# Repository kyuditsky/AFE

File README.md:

AFE 230V 16A

Phoenix Contact
BC Modular Housing

AFE 230v_16a buildnotes
addendums at bottom

1/14/25

***

https://media.digikey.com/pdf/data%20sheets/phoenix%20contact%20pdfs/bc_series_installation_component_housing.pdf

***

***

https://github.com/erichelgeson/Kicad-STM32
add legacy symbols:
symbol editor > File > import

manage symbols > migrate

***

BC71,6 OT-U11

i/o
---
MSTBVA_2,5_2-G-5,08		#LPC 2,5/2-ST-5,08	plug 16A / 320V
				#1792757		12A / will actually fit
				#MVSTBW 2,5/ 2-ST-5,08
j1	VO_pn
j2	K_io
j3	I_pn

MCV_1,5_6-G-3.81
j4	DGND
	3v3
	A0
	A1
	A2
	D0

footprints
TSOT-23-5	opamps
SOT-23		regulator
SOIC-7		optocoupler
SOIC-8		currentsensee

A5?		#A2
3v3in?

***
1/15/25
Blackpill STM32 will be on separate daughterboard

added HBUS connector to schema

***
HBUS-B SET BK - Protective cap
2278173
***

Spec:
Contact 1..4	power
contact 5..16	signal
Air clearances and creepage distances
... to the DIN rail At least 0.23 mm
... between one another At least 0.13 mm
... between power and signal At least 0.8 mm
Current carrying capacity for each contact
3 A, maximum total current 25 A

***
1/16/25

generated BOM from schema
refined layout and i/o port locations

request to swap A2 to A0 and slide down accordingly
	basically current on the left, voltage on right
	of J4

***
1/23/25

Housing:

HBUS 71,6-16P-1S BK - DIN rail bus connectors	2896296		#digikey 10 instock - 33.54

full set
BC 71,6-SKT-U11-7035+4SPTA6 - Housing set	1456985		#larger space on PCB2-8
								#11mm connector space on PCB1

Base:
BC 71,6 UT HBUS BK - Mounting base housing	2896267		#8.53

upperhousing UT11
BC 71,6 OT U11 KMGY - Upper housing part	2896050		#5.66

housing cover:
BC 71,6 DKL S TRANS - Housing cover		2896128		#4.93

inter-PCB connection:

ESW-106-12-G-D		6 pos, 11.05mm above pcb, gold plated, double row (12pos total)
			2.54 pitch, THT

2.54 pin header		underside of connecting pcb
			
	11.05mm + 2.54mm = 	13.59mm stack height
				perfect stack from pcb1 to pcb4

***
1/24/25

added copper pours from current i/o to U5

blackpill pinout in PCBnew appears incorrect to documentation

footprint matches:
	https://uglyduck.vajn.icu/STM32_Pills/BlackPill_STM32F103_Pinout.jpg

current blackpill:
	https://cdn-shop.adafruit.com/970x728/4877-03.jpg

updated with:
	https://github.com/MSZ98/Blackpill-KiCad-library

STEP files imported into Fusion

	MCV_1,5_6-G-3.81 	&	MCVR 1,5/ 6-ST-3,81
	1803468				1827169
		will not work, move socket towards pcb edge

	MSTBVA_2,5_2-G-5,08	&	MVSTBW 2,5/ 2-ST-5,08
	1755736				1792757
		will NOT work
		connectors should rotate
		and new connector should be chosen

Fillets on main PCB edges are only needed if filler plugs are to be used

SPTAF 1/ 5-3, 5-IL	supplied with housing kit, 11mm deep
	16A 160V

1862275
SPTAF 1/ 2-5,0-IL	2 terminal
	16A 320V	made to order	in stock at mouser
			IL vs EL

SPTAF 1/ 4-5,0-EL	4 terminal	#use 6 terminal for signal i/o
1862437			

AC inputs should be at least 2.5mm wire

***
https://electronics.stackexchange.com/questions/645255/4-layer-board-clearance-and-stack-up-for-230v

creepage / clearance

remove gnd plane from around I_inputs & Vp/n

***
1/27/25

SPTAF 1/ 6-5,0-EL
1862453

2202302 upper housing 11,11,22,00	restricted availability

in order to use SPTA-THR 2,5/ 6-5,0 P26		#for 12 awg wire AC inputs
need to swtich to UT22 upperhousing

1071206
SPTA-THR 1,5/ 6-5,08 R56	#might work, wire size 16awg
				#nonstocked at mouser
				#instock at digikey

***
02/02/25

Mouser Order sent			order#273566739

ordered two MKDSN 1.5/2-HT		1985849		rated 13A/320v
	for Ki/o
AC inputs: MKDSN 2.5/3-5.08-BK		1800882		
	(2.5/6 out of stock)
Signal Out: MKDS 1.5/6			1715190

********

02/06/25

revisiting pcb2-8
	& headers between
	see 01/23/25		#ESW-106-12-G-D

JLCPCB standard pcb thickness = 1.6mm

space between each:

pcb1-2	3,55mm
pcb2-3	3,45
pcb3-4	3,45
pcb4-5	3.45		#if blackpill is socketed, void pcb5-8
pcb5-6	3,45
pcb6-7	0,95
pcb7-8	-0.3		#pcb7&8 cannot co-exist
pcb8-9	1.25		#pcb9 replaces fitted cover

>>>pcb1 edge dimensions are incorrect
	edge cutouts in middle are too deep
	HBUS connector is in the wrong spot
>>fixed hbus placement
	did not change edgecuts
	current edge cut and drawing differ 0,45mm	
		#radius of curve 1,2mm but edges are 0,75mm offset
		#hbus location callout uses the 0,75mm line

considering shifting intrapcb connector to the left	#implemented
	reasoning: allows for pcb 2 to be installed (cutout is close to mounting fin ~1.5mm)

****
02/16/25

added pcb5-7 with kludge and copper pours
added kludge to other pcbs

added silkscreen on pcb9

****

02/27/25

PCBs arrived, Parts arrived
putting it together:

pcb8 does not fully lock into bottom case
	top base needs a support remove as well
	*use pcb7 instead (may still need to remove support
	pcb8 gnd plane net is wrong

overall, edgecuts are correct

c1-2 are 0402?		#my bad
	footprint is 0603

the intrapcb connectors looks good
make cutout in pcb2,3 larger, but fits for now

U4, solidstate relay, just barely fits under pcb2

typical female 2.54mm header, from pcb1 to pcb3, stacks directly underpcb3

	pcb3-pcb5 approximately the same thing
	could probably use pcb1, 3, & 5 for a 3 board arrangement

****
05/05/25 - meeting

issues soldering the ground plane pads - with thermal relief

plan to design to pick and place, still jlcpcb?
	mitigate some of the issues possibly due to soldering

testing feels like a waste of time, i dont always know what im looking at

dont have a good grasp of the details of the scope

single ended two op amps, gnd and point
	A0 and A1 subtract one from another to get ------

differential has 3 op amp
	does the subtraction

single
a0 ref to gnd
a1 ref to gnd
	note divider from 3V to GND to give 1.5v at input buffer

diff r19 r21 should be 500, r20 1k
r22 r23 dnp

everycircuit - simulator

testing setup >>
single ended (two opamp)
	wavegen 1 & gnd to V0p & V0n
	scope 1+ to A0			1+ 
	scope 1- to A1			scope 1- to dgnd
	3v3V+ to 3v3
	gnd to DGND
waveform passed through without power to board
	1.5v observed at r35/r36

differential
	wavegen 1 & gnd to V0p & V0n
	scope 1+ to A0
	scope 1- to dgnd
	3v3V+ to 3v3
	gnd to DGND
	
	0.6v observed at r35/r36
***	
	r22/r23 should be DNP
	r19/r21 should be 500ohm

****
updated guidance:
Focus on single ended:

	two sides are separate paths, test 1 path at a time
	
	V0p - wave to A0 - scope
	scope1- to dgnd

	V0n - wave to A1 - scope
	scope1- to dgnd

	(need to check for 1.5V at r15/r17; r16/18)

07/09/25

differential board, 3 opamps
	depopped r22, r21
	lifted a trace near r22, 
		determined iron too hot with narrower tip

Lifted R19 pads while desoldering
	buss wired from R20 to U1-4 & R22
		cut old R22 trace to A0
		R19 is now on R22 pads
		replaced to 510ohm
R21 now 510ohm
R20 in place at 1k

hot glue placed over cut A0 trace
	(exposed gnd plane)

*******
08/13/25 10:00a

identify and order just the differential parts
	to be tested via V0/V1_sense on HBUS footprint
	using the digilent waveform gen

initial DNP:	
	r1-12 	voltage dividers 
	d1-4	zener diodes
	c1 c2	capacitors	sized up to 0603

V0_sense starts: 	
	r13 	499k ohm 	#consider a 0ohm resistor
	c1	1nf
	r15 	20k (to 3vREF)	#Voltage divider to non-inverting input U1
	r17	20k (to gnd)
	r19	510		#feedback R
	
	r24	1k		#buffer to non-inverting U3
	r27	1k		#buffer to 1.5vREF	(r35&r36 20k divider)

V1_sense starts:
	r14 	499k ohm 	#consider a 0ohm resistor
	c2	1nf
	r16 	20k (to 3vREF)	#Voltage divider to non-inverting input U2
	r18	20k (to gnd)
	r21	510		#feedback R
	
	r25	1k		#buffer to inverting U3
	r26	1k		#U3 feedback

common components:

	U1-3	AD8528		#opamps		TSOT23-5
	d1-4	pdz36b		#36v zener diodes, order but dnp

	r20	1k		#ties both sides together
	r35	20k		#1.5vREF
	r36	20k		#1.5vREF
	U7	REF3030		#3V regulator	SOT23

	r39	0		#gnd to dgnd
	C5,6,10	0.1uF		#filtercaps

notes:
	look at r20 net, should it be connected directly to output of u1
		#sent to nathan
		confirms r20 should bridge U1 out to U2 out
		updated PCBnew

	populate PCB a few components at a time & test
		looking at you 1.5vREF

AFE_230v_16a rev.2 aug25
	changelog
	
	changed r20 to u1 & u2 outputs
	added thermal relief to D1 D2 earth connections
	added thermal relief to I_p & I_n fill zones
	rotated U4 to keep traces on F.cu
	added AVDD indicator LEDs to main pcb

2pm
lets order the updated pcb and mouser components by end of day

	look into jlcpcb pick and place and smaller components (0402)

AFE_diff_schematic
	focus on just the differential section
		using 0402 components
****
new plan (again)
	we are ordering a new pcb (because of R20)
	pick and place the components on the new pcb (adjust footprints accordingly)
		keeping all R footprints for now, all C footprints are 0603

	U1-3, U6, LEDs, & R29 non- placeable
	D1-4 are extended ($3.00 per extended component type)
	U7 is extended, opted out

	ordering 5 boards, populating 2 ($0.75 more to populate 5 as opposed to 2)
				and rev1 single end works without revision
				but. lets keep some blank boards
	16.17 for pcb+pcba
	9.97 shipping
	-9.00 coupon
	total: 18.05

***

08/18/25
	plan to order female pin headers from Adafruit

	leave off R34 from auto-populating
		or add 0 ohm jumper

	need to organize spreadsheets better

****
09/08/25

ordered more microhook test leads

looking over mouser order

	AC signal inputs - 1
	Signal Outputs - 1
	K i/o - 2

	opamps - 10
	U4 Relay - 1
	U7 3v ref - 5
	U5 current sense - 2
	R29 big R - 4
	
	pcb4 elevated socket - 2

R20 could have been rerouted without a via to B.Cu
removed thermal relief from Ip,In

dont auto-populate r30,r31 (only pop for opamp current sensing with r29)

test before populating r1-12 (voltage dividers)

r13,14, r22,23 will need hand populating (extended componenets)
	#should not have popped r22,r23, but will test waveform thru A0,A1
5v,3v3 LED hand pop

header pins as needed
	V1/V0 test points
	DGND > D0 header
		dgnd, 3v, A0,A1,A2,D0

3v3, 5v LED test good

3v3 supply, no opamps
	3.317v at 3v3
	2.997v at 3vref
	1.483v at 1.5vref

#same divider but different nets?
#1.5vref and r15/r17 & r16/r18

power looks good, continueing to add opamps

Should not have popped r22,r23 for differential setup, but will test waveform thru A0,A1
	V0_sense thru to A0
	V1_sense thru to A1
		both test good without power to board, no offset

		with 3v3 power to board, look good, adds a 1.46v(A0) & 1.47v(A1) offset
			with or without waveform input (5v amplitude)
			scope range 1v/div

going to remove r22,r23
	r22,23 depopped without trouble

3v3 supply, opamps installed
r27, 1.5vref = 1.497v
3v0ref = 3.0v
3v3 = 3.317v
1.5vref = 1.497v (r35/r36)

power still looks good

3v3 to board

W1 to V0_sense
W2 to V1_sense

1+ to A0
1- to dgnd

no longer the 1.5v offset
	output (A0) looks promising, especially with Sine wave inputs
	scope range needs to be dialed down to 100mV/div or less

can add 
	Vin dividers (r1-12)
	input/signal I/O
	blackpill header
	Ki/o relay
& option for either 
		current sense IC (depop r30,31)
		or R29 & opamp

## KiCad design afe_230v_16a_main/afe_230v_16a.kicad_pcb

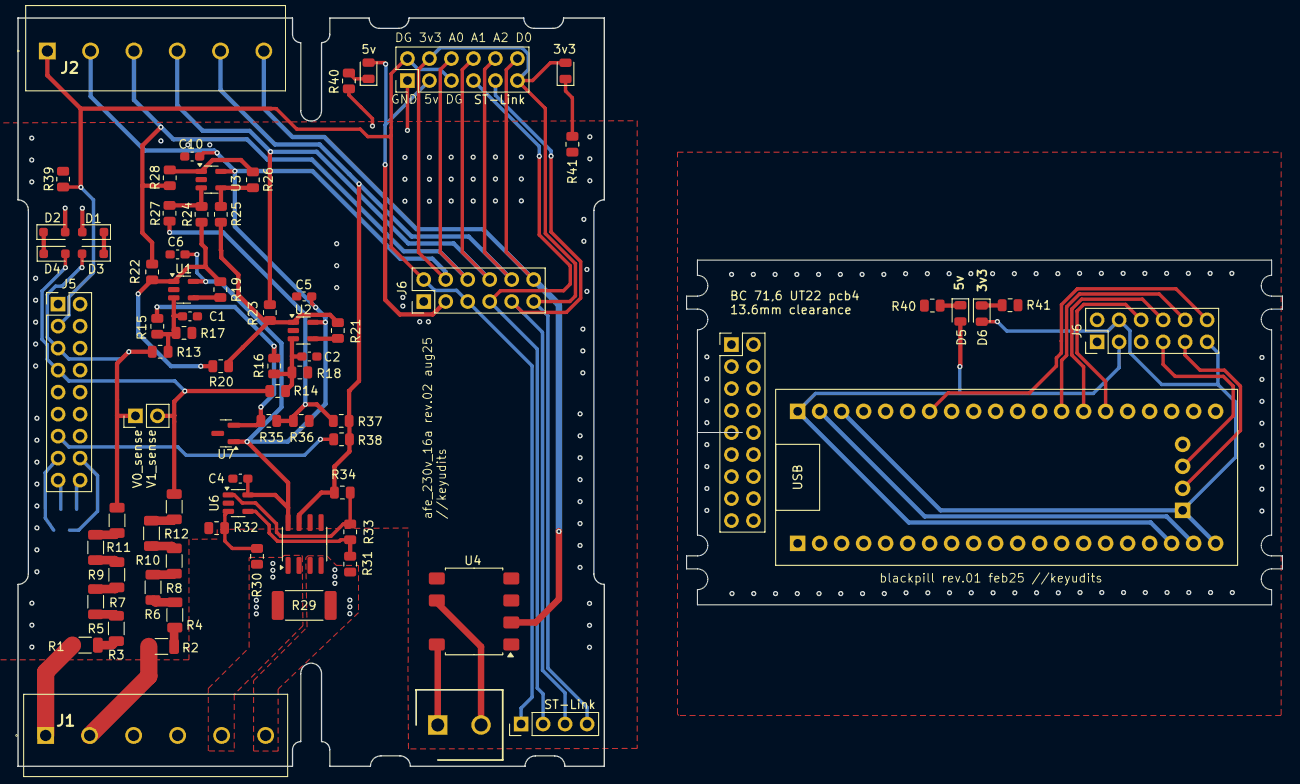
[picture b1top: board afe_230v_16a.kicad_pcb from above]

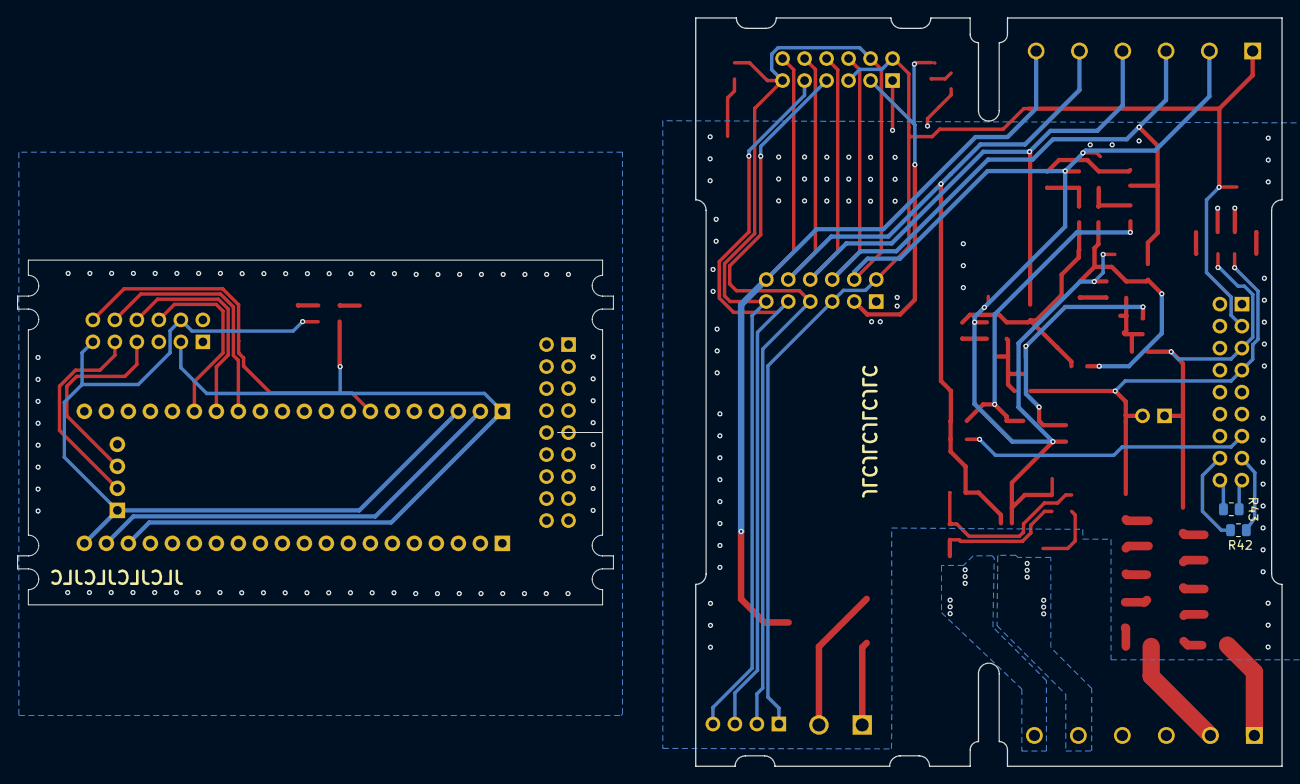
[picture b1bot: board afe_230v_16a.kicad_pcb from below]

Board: 2 copper layers, 145.9 x 86.4 mm, 76 parts (2 on the bottom side), 61 nets.

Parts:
3v3, 5v: LED; LED_0805_2012Metric
C1, C2: 1nF; C_0603_1608Metric_Pad1.08x0.95mm_HandSolder
C4, C5, C6, C10: 0.1uF; C_0603_1608Metric_Pad1.08x0.95mm_HandSolder
D1, D2, D3, D4: PDZ36B; D_SOD-323_HandSoldering
D5, D6: LED; LED_0805_2012Metric
J1: MKDSN 2,5/ 6-5,08; 1989405
J2: MKDS 1,5/ 6; 1715190
J5, J5#2: HBUS16; PinHeader_2x09_P2.54mm_Vertical
J6, J6#2, J6#3: pinheader_2x6_socket; PinHeader_2x06_P2.54mm_Vertical
J**: SHDR2W130P0X500_1X2_1000X810X1000P; 1985849_SHDR2W130P0X500_1X2_1000X810X1000P
R1, R2, R3, R4, R5, R6, R7, R8, R9, R10, R11, R12: 680K; R_1206_3216Metric
R13, R14: 499K; R_0805_2012Metric
R15, R16, R17, R18, R35, R36: 20K; R_0805_2012Metric
R19, R21: 0K; R_0805_2012Metric
R20, R24, R25, R26, R27, R28: 1K_dnp; R_0805_2012Metric
R22, R23: 33R2; R_0805_2012Metric
R29: 0R005; R_2512_6332Metric_Pad1.40x3.35mm_HandSolder
R30, R31, R32, R33, R34, R37: 1KR; R_0805_2012Metric
R38: 0K_dnp; R_0805_2012Metric
R39, R42, R43: 0; R_0805_2012Metric
R40, R40#2, R41, R41#2: 2.2k; R_0805_2012Metric
ST-Link: Conn_01x04_STlink_pinheader; PinHeader_1x04_P2.54mm_Vertical
U1: TSOT-23-5
U2: AD8538; TSOT-23-5
U3, U6: AD8538_dnp; TSOT-23-5
U4: AQH3223A; SSO-7-8_6.4x9.78mm_P2.54mm
U5: ACS711xLCTR-25AB; SOIC-8_3.9x4.9mm_P1.27mm
U7: REF3030; SOT-23
U10: BlackPill_F4_SWI; Blackpill_F4_SWI

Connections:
/1V5_REF: R27.2, R35.1, R36.2, R37.2
/3V0_REF: R15.2, R16.2, R35.2, U7.2 (OUT)
/3V3: 3v3.2 (A), C4.1, C5.1, C6.1, C10.1, D6.2 (A), J2.2, J6.4, J6.11, J6#2.4, J6#2.11, J6#3.4, J6#3.11, ST-Link.4, U1.5 (V+), U2.5 (V+), U3.5 (V+), U5.8 (VCC), U6.5 (V+), U7.1 (IN), U10.20 (3V3), U10.38 (3V3), U10.41 (3V3)
/5v: 5v.2 (A), D5.2 (A), J6.3, J6#2.3, J6#3.3, U10.18 (5V), U10.40 (5V)
/15a: J5.15, J5#2.15, R42.1
/15b: J5.16, J5#2.16, R42.2
/16a: J5.17, J5#2.17, R43.1
/16b: J5.18, J5#2.18, R43.2
/24V: J5.1, J5#2.1
/A0: J2.3, J6.6, J6#2.6, J6#3.6, R22.2, R28.2, U10.26 (A0)
/A1: J2.4, J6.8, J6#2.8, J6#3.8, R23.2, U10.27 (A1)
/A2: J2.5, J6.10, J6#2.10, J6#3.10, R34.2, R37.1, R38.1, U5.7 (VIOUT), U10.28 (A2)
/CAN_hi: J5.9, J5#2.9
/CAN_lo: J5.11, J5#2.11
/D0: J2.6, J6.12, J6#2.12, J6#3.12, U4.2, U10.34 (B0)
/DGND: J2.1, J5.3, J5#2.3, J6.2, J6.5, J6#2.2, J6#2.5, J6#3.2, J6#3.5, R39.2, ST-Link.1
/DIO: J6.9, J6#2.9, J6#3.9, ST-Link.3, U10.42 (SWDIO)
/I0_sense: J5.13, J5#2.13, R38.2
/I_n: J1.6, R29.2, R31.2, U5.3 (IP-), U5.4 (IP-)
/I_p: J1.5, R29.1, R30.1, U5.1 (IP+), U5.2 (IP+)
/K0_on: J5.2, J5#2.2
/K0_status: J5.6, J5#2.6
/K1_on: J5.4, J5#2.4
/K1_status: J5.8, J5#2.8
/K_i: J**.1, U4.8
/K_o: J**.2, U4.6
/SCK: J6.7, J6#2.7, J6#3.7, ST-Link.2, U10.43 (SWCLK)
/V0_n: J1.2, R2.1
/V0_p: J1.1, R1.1
/V0_sense: D3.2 (A), J5.5, J5#2.5, R11.2, R13.1
/V1_sense: D4.2 (A), J5.7, J5#2.7, R12.2, R14.1
/V2_sense: J5.10, J5#2.10
/V3_sense: J5.12, J5#2.12
/V4_sense: J5.14, J5#2.14
Earth: C1.2, C2.2, C4.2, C5.2, C6.2, C10.2, D1.2 (A), D2.2 (A), J6.1, J6#2.1, J6#3.1, R17.1, R18.1, R32.2, R36.1, R39.1, R40.1, R40#2.1, R41.1, R41#2.1, U1.2 (V-), U2.2 (V-), U3.2 (V-), U4.1, U4.3, U4.4, U5.5 (GND), U6.2 (V-), U7.3 (GND), U10.19 (G), U10.39 (G), U10.44 (GND)
unnamed: D1.1 (K), D3.1 (K)
unnamed: D2.1 (K), D4.1 (K)
unnamed: 5v.1 (K), D5.1 (K), R40.2, R40#2.2
unnamed: 3v3.1 (K), D6.1 (K), R41.2, R41#2.2
unnamed: R1.2, R3.1
unnamed: R2.2, R4.1
unnamed: R3.2, R5.1
unnamed: R4.2, R6.1
unnamed: R5.2, R7.1
unnamed: R6.2, R8.1
unnamed: R7.2, R9.1
unnamed: R8.2, R10.1
unnamed: R10.2, R12.1
unnamed: R9.2, R11.1
unnamed: R19.2, R20.1, R22.1, R24.1, U1.1
unnamed: R20.2, R21.2, R23.1, R25.1, U2.1
unnamed: R26.2, R28.1, U3.1
unnamed: R33.2, R34.1, U6.1
unnamed: C1.1, R13.2, R15.1, R17.2, U1.3 (+)
unnamed: R19.1, U1.4 (-)
unnamed: C2.1, R14.2, R16.1, R18.2, U2.3 (+)
unnamed: R21.1, U2.4 (-)
unnamed: R24.2, R27.1, U3.3 (+)
unnamed: R25.2, R26.1, U3.4 (-)
unnamed: R30.2, R32.1, U6.3 (+)
unnamed: R31.1, R33.1, U6.4 (-)

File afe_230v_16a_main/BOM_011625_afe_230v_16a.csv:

"Reference","Value","Datasheet","Footprint","Qty","DNP"
"C1,C2","1nF","~","Capacitor_SMD:C_0402_1005Metric","2",""
"C3,C7,C8,C9,C12,J1,J2,J3,T7,T8,T9,T10,T11,T16,T17","~","-- mixed values --","-- mixed values --","15",""
"D1,D2,D3,D4","PDZ36B","~","Diode_SMD:D_SOD-323F","4",""
"J4","MCV 1,5/ 6-G-3,81","~","Connector_Phoenix_MC:PhoenixContact_MCV_1,5_6-G-3.81_1x06_P3.81mm_Vertical","1",""
"J5","HBUS16","~","Connector_PinHeader_2.54mm:PinHeader_2x09_P2.54mm_Vertical","1",""
"P1","06-14-03_rectifier","","","1",""
"R1,R2,R3,R4,R5,R6,R7,R8,R9,R10,R11,R12","680K","~","Resistor_SMD:R_1206_3216Metric","12",""
"R13,R14","499K","~","Resistor_SMD:R_0805_2012Metric","2",""
"R15,R16,R17,R18,R35,R36","20K","~","Resistor_SMD:R_0805_2012Metric","6",""
"R19,R21","0K","~","Resistor_SMD:R_0805_2012Metric","2",""
"R20,R24,R25,R26,R27,R28","1K_dnp","~","Resistor_SMD:R_0805_2012Metric","6","DNP"
"R22,R23","33R2","~","Resistor_SMD:R_0805_2012Metric","2",""
"R29","0R005","~","Resistor_SMD:R_2512_6332Metric_Pad1.40x3.35mm_HandSolder","1",""
"R30,R31,R32,R33,R34,R37","1KR","~","Resistor_SMD:R_0805_2012Metric","6",""
"R38","0K_dnp","~","Resistor_SMD:R_0805_2012Metric","1","DNP"
"U1","","https://www.analog.com/media/en/technical-documentation/data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","Package_TO_SOT_SMD:TSOT-23-5","1",""
"U2","AD8538","https://www.analog.com/media/en/technical-documentation/data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","Package_TO_SOT_SMD:TSOT-23-5","1",""
"U3,U6","AD8538_dnp","https://www.analog.com/media/en/technical-documentation/data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","Package_TO_SOT_SMD:TSOT-23-5","2","DNP"
"U4","AQH3223A","https://mediap.industry.panasonic.eu/assets/imported/industr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","Package_SO:SSO-7-8_6.4x9.78mm_P2.54mm","1",""
"U5","ACS711xLCTR-25AB","http://www.allegromicro.com/~/Media/Files/Datasheets/ACS711-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","Package_SO:SOIC-8_3.9x4.9mm_P1.27mm","1",""
"U7","REF3030","http://www.ti.com/lit/ds/symlink/ref3033.pdf","Package_TO_SOT_SMD:SOT-23","1",""
"U8","adc_sym","","","1",""
"U9","YAAJ_BlackPill","","STM-32:YAAJ_BlackPill_SWD_2","1",""
"U17","1_element_2_current","","","1",""
"U20","watt_hour_meter_bidirectional","","","1",""

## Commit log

2025-01-14 011425 end of day
2025-01-15 updated schema
2025-01-15 began PCBA layout
2025-01-16 alternate layout
2025-01-21 added pcb2&3 board outlines, adjusted i/o
2025-01-21 pleased with layout, onto wiring
2025-01-21 refined layout, added MouserBOM
2025-01-22 adjusted HBUS, DNP, & fixed A5toA2
2025-01-22 initial routing
2025-01-23 located daughterboard & updated connector
2025-01-24 changed BP footprint, added stlink connection, added 3d models
2025-01-27 swapped connectors
2025-01-27 updated BOM
2025-02-02 BOM ordered
2025-02-06 fixed hbus location, added bc71,6 edgecuts'
2025-02-06 adjusted inter-pcb-connector location, added edgecuts pcb2,3,4,8,9
2025-02-16 refined BC71,6 edgecuts for pcb2-9
2025-02-19 added 15/16 0ohm resistors
2025-02-19 gerbers plotted, pcbs on order
2025-02-27 Updated buildnote
2025-08-13 changed r20 net
2025-08-13 adjusted PCB for rev.2 aug25
2025-08-13 added JLC BOM & CPL
2025-08-19 added and refined aug25 Mouser order
2025-09-08 populated&tested rev2 differntial board
2025-09-08 updated readme.md with buildnote
2025-10-21 populated single ended rev2.0
2025-10-24 tested single ended rev2.0
2025-11-06 upgraded to kicad 9.0.6
